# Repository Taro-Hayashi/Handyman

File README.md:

# Handyman マクロパッド ビルドガイド（[English](https://github.com/Taro-Hayashi/Handyman/blob/main/README_EN.md)）
- [キット内容](#キット内容)
- [準備](#準備)
- [はんだ付け](#はんだ付け)
- [組み立て](#組み立て)
- [キーのカスタマイズ](#キーのカスタマイズ)
- [その他](#その他)

## キット内容

||部品名|数| |
|-|-|-|-|
|1|メインボード|各1||
|2|バックプレート|1||
|3|ミドルプレート1|1||
|4|ミドルプレート2|1||
|5|保護プレート|1||
|6|ネジ（短）|9|3mm|
|7|ネジ（中）|3|5mm|
|8|ネジ（長）|12|6mm|
|9|スペーサー（短）|12|3mm|
|10|スペーサー（中）|3|4mm|
|11|ダイオード|26|1N4148|
|12|リセットスイッチ|1||
|13|ロータリーエンコーダ（ダイヤル）|1|EC11互換品|
|14|ノブ|1||
|15|ロータリーエンコーダ（ホイール）|2|EVQWGD001|
|16|ゴム足|7||
|17|Pro Micro|1||

### キット以外に必要なもの
|部品名|数||
|-|-|-|
|キースイッチ|22|[Kailh choc V1](https://shop.yushakobo.jp/collections/all-switches/products/pg1350)、[Kailh Choc V2](https://shop.yushakobo.jp/collections/all-switches/products/kailh-choc-v2)、[Lofree ロープロファイル](https://shop.yushakobo.jp/products/8381)|
|キーキャップ|22|V1は[専用キーキャップ](https://shop.yushakobo.jp/collections/keycaps/For-Choc-v1)、V2,Lofreeは[CherryMX互換](https://shop.yushakobo.jp/collections/keycaps/cherry-mx-%E4%BA%92%E6%8F%9B-%E3%82%AD%E3%83%BC%E3%82%AD%E3%83%A3%E3%83%83%E3%83%97)です。|
|Micro USB ケーブル|1||

### 必要な工具
|工具名|
|-|
|はんだごて|
|はんだ|
|精密ドライバー|
|ニッパー等ダイオードの足を切れるもの|
|マスキングテープ等絶縁できるテープ|
|エポシキ接着剤|

### オプション

LEDを光らせる場合
|部品名|数||
|-|-|-|
|[SK6812MINI-E](https://shop.yushakobo.jp/products/sk6812mini-e-10)|22|バックライト|
|[WS2812B](https://shop.yushakobo.jp/products/a0800ws-01-10)|6|アンダーグロー|

色違いのアクリルプレート
|部品名|数||
|-|-|-|
|[キーボードアクリルプレート（左手用）](https://shop.yushakobo.jp/collections/services/products/keyboard_acrylic_plate?variant=43890200740071)|||
|[キーボードアクリルプレート（右手用）](https://shop.yushakobo.jp/collections/services/products/keyboard_acrylic_plate?variant=43890207719655)|||
|[キーボードアクリルプレート（バックプレート）](https://shop.yushakobo.jp/collections/services/products/keyboard_acrylic_plate?variant=43890215583975)|||

Bluetooth接続について
 - [電池ボックスの使い方](ble.md) 

## 準備
左右どちらで作るかを選びます。  

Pro MicroはMicro-USB端子をエポシキ接着剤で補強します。  
  
両サイドと手前側のはんだ付けされてるところに少し厚めに塗ります。端子の中に入り込まないように気を付けます。
  
乾燥させている間にはんだ付けを進めましょう。  

## はんだ付け
はんだ付けのやり方は動画で見るとわかりやすいです。  
パーツは思ったより壊れないので落ち着いて作業すると失敗しにくいです。  
 - ホームセンターのDCMさんの解説動画(58秒～)  

### LEDのはんだ付け（オプション）
LEDを取り付ける場合はメインボードに最初にはんだ付けします。  
 - [LEDの取り付け方](led.md)  

### ダイオード、リセットスイッチのはんだ付け
D1からD26までダイオードを取り付けます。  
足を曲げて裏から差し込みます。  
  
ダイオードには向きがあります。三角形の先の棒と黒線を合わせましょう。  

表で更に足を曲げて抜けないようにします。  
  
ダイオードと並行に曲げるとあとでキースイッチに干渉しにくいです。

はんだ付けをして足を切ります。  

リセットスイッチを裏から差し込み表ではんだ付けします。  
  
フラックスクリーナーを使う人はここで表面を綺麗にしておきましょう。  

### ピンヘッダーのはんだ付け（Pro Microはまだはんだ付けしません）
Pro Microの取り付け場所にピンヘッダーの短い側を差し込みます。
  
位置決めのためにPro Mioroを乗せますが、はんだ付けはせず表にします。

メインボードにピンヘッダーをはんだ付けします。
  
Pro Microをいったん外します。

### キースイッチのはんだ付け

ここの二つのキースイッチは足がPro Microと干渉するので短く切ります。
  
差し込んだ状態で短く切りましょう。
  
Choc V2の場合は3本の足を、Choc V1では2本の足と固定用品の一つを短くします。

全てのスイッチをはんだ付けします。　　

### Pro Microのはんだ付け
隠れてしまうダイオードD1の方向が合っているか、キースイッチの足がはんだ付けされているかを再度確認してください。  
Micro-USB端子がショートしやすいのでカプトンテープやマスキングテープなどで絶縁します。  
  
足をニッパーで切ったらはんだ付けします。

### 動作テスト
ロータリーエンコーダーを取り付ける前にPro Microに動作ソフト（ファームウェア）を書き込んで動作確認をしましょう。  
キットとPCをUSBケーブルでつないでください。   

下のwebサイトにアクセスしてください。
- https://remap-keys.app/catalog/dTmFWd6gilf5ziDWE1TR/firmware

テストファームウェアを選んでFLASHします。

キット裏面のリセットスイッチを押すとArduino Microが現れるので、クリックして接続します（初回のみリセットスイッチを2回押す必要があることがあります）。

書き込みが完了したらウィンドウを閉じて大丈夫です。

アドレスバーやテキストエディタを使ってすべてのスイッチが反応することを確かめてください。

Remapを使ってファームウェアの更新ができない場合は、QMK Toolboxをお試しください。
- [QMK Toolboxを使ったファームウェア更新方法](firmware.md)

### ロータリーエンコーダーのはんだ付け
SW12、SW14に表からホイール型のロータリーエンコーダーを取り付けます。  
ピンの位置を確認してツメを穴に差し込みます。  

ツメを穴に引っかけてからピンを穴に差し込みます。   
   
ピンを曲げてしまわないように注意してください。  
  
差し込めたらはんだ付けします。  

SW20に表からダイヤル型のロータリーエンコーダーを取り付けて裏からはんだ付けします。  
  
クリップの部分ははんだ付けしなくても構いません。  

お疲れ様でした。再び動作を確認して問題がなければはんだ付けは終了です。

## 組み立て
USBケーブルを抜いてプレートを組付けます。  
アクリルからは保護フィルムを剥がしてください。割れやすいので気をつけましょう。  

メインボードのネジ穴にスペーサー（短）をネジ（短）で取り付けてミドルプレート1（透明）を嵌めます。
   
ここの3箇所は表側はネジではなくスペーサー（中）で止めます。

ミドルプレート2とバックプレートをネジ（長）で止めます。
 
ゴム足も貼りました。

表に保護プレートをネジ（中）で取り付けましょう。

マイナスドライバーでノブを取りつけ、キーキャップを付けたら完成です。

先ほどと同様の手順でRemap用のファームウェアに更新しましょう。
- https://remap-keys.app/catalog/dTmFWd6gilf5ziDWE1TR/firmware

## キーのカスタマイズ
こちらのサイトにGoogle Chrome（Chromiumベースのブラウザ）でアクセスしてください。
- Remap https://remap-keys.app

左を選んで進んでいくとダイアログが出てキーボードを選択できます。  
  
選択して接続してください。
  
標準ではUS配列設定でのClip Studio Paintにあわせたキーマップになっています。  

### キーマップの保存と復元
⇔アイコンで作ったキーマップを保存することができます。  
  
作ったキーマップを共有することもできるので是非お試しください。

### 左右を変える
レイアウトオプションで左右を変えることができます。  

### キーを設定する
下のキー一覧からドラッグアンドドロップし、変更が終わったら右上のflashボタンを押すと反映されます。  
  
また、USキーボードとJISキーボードはFlashの下のプルダウンから変更できます。OSの設定に合わせてください。

### 修飾キーとの組み合わせを設定する
上のキーボードのキーをクリックすると設定画面になります。
  
修飾キーと同時押ししたいキーを検索し、同時押ししたい修飾キーにチェックを入れます。

Hold-Tapもここから設定できます。

### ロータリーエンコーダーを設定する
丸いキーの左下をクリックすると時計回り、反時計回り、押し込みを切り替えることができるので、それぞれにキーを割り当てます。

### 特殊なキーを設定する
FUNCTIONSタブのVIA USER KEYにあらかじめ用意されたショートカットキーがあります。

### LEDを調整する
このボタンで発光方法を変更することができます。

## その他

### ファームウェアのフォルダ  
https://github.com/Taro-Hayashi/qmk_firmware/tree/tarohayashi/keyboards/tarohayashi/_archive/handyman

### プレートのデザインデータ  
[handyman_plates.zip](https://github.com/Taro-Hayashi/Handyman/releases/latest/download/handyman_plates.zip)  
発注先のルールに沿ってデータを修正してください。  

### 販売サイト
- 遊舎工房: https://shop.yushakobo.jp/collections/keyboard/products/2795   
- BOOTH: https://tarohayashi.booth.pm/items/3208122

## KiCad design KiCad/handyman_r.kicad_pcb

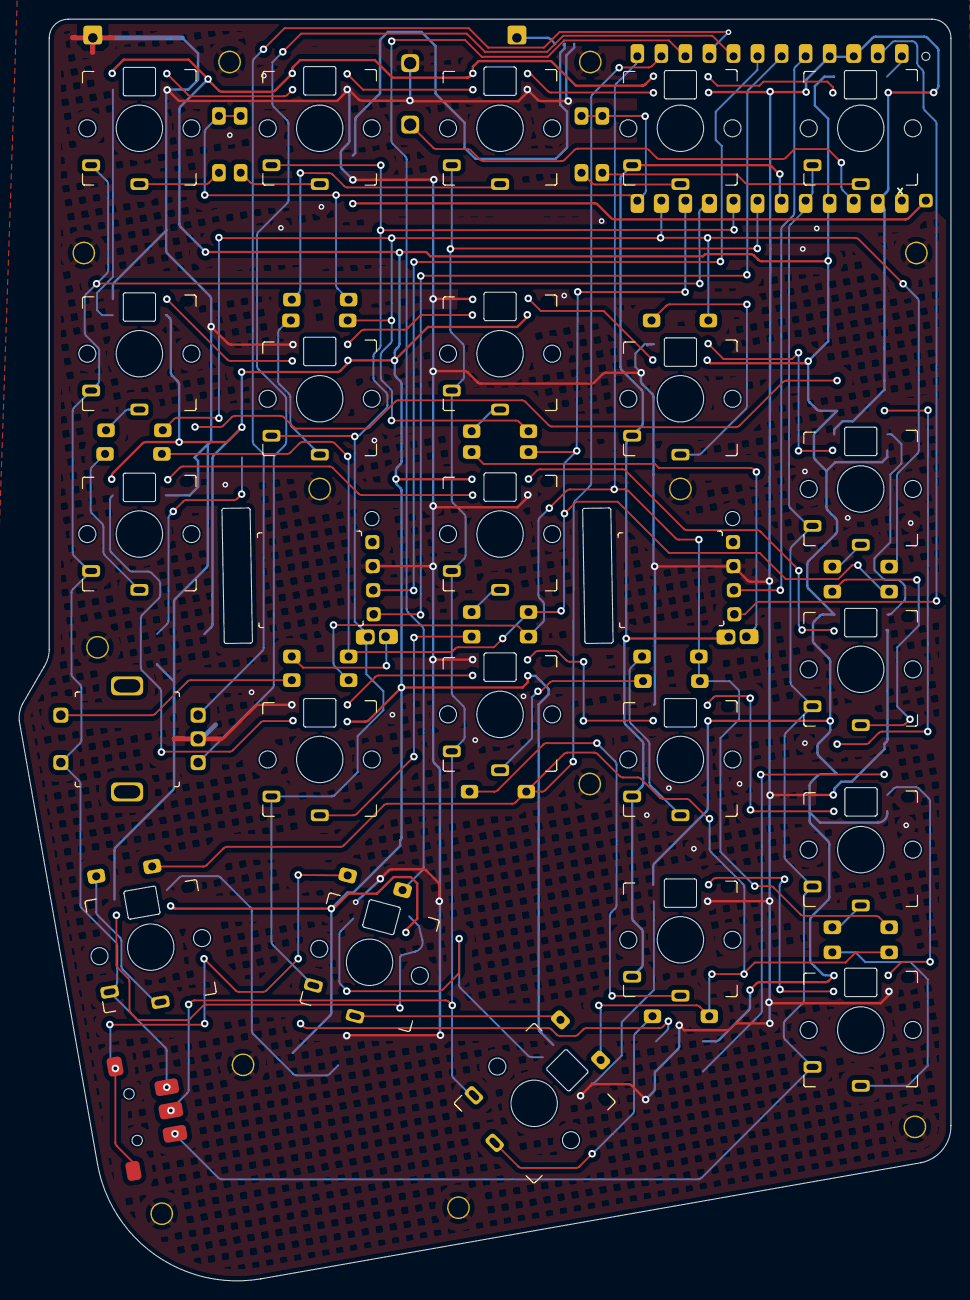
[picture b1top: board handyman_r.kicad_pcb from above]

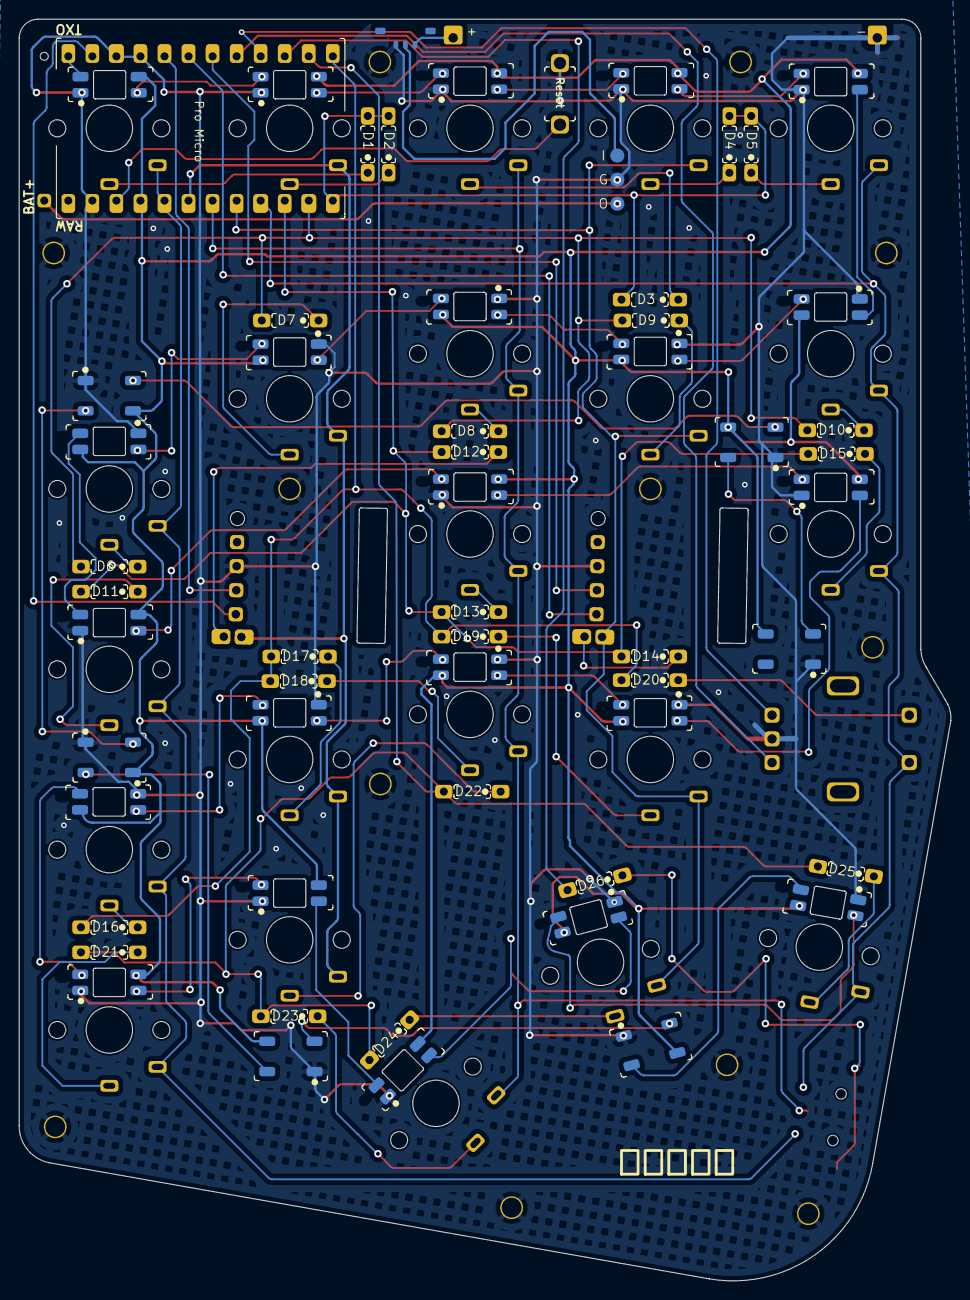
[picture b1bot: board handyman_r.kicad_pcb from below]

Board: 2 copper layers, 98.4 x 133.2 mm, 94 parts (67 on the bottom side), 74 nets.

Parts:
BL1, BL2, BL3, BL4, BL5, BL6, BL7, BL8, BL9, BL10, BL11, BL12, BL13, BL14, BL15, BL16, BL17, BL18, BL19, BL20, BL21, BL22: SK6812MINI-E; LED_SK6812MINI-E_Backlight
D1, D2, D3, D4, D5, D6, D7, D8, D9, D10, D11, D12, D13, D14, D15, D16, D17, D18, D19, D20, D21, D22, D23, D24, D25, D26: D; DIP_Diode 2
H1, H2, H3, H4, H5, H6, H7, H8, H9, H10, H11, H12: Hole; Hole_2mm_M2_PTH
Knob: Rotary_Encoder; Encoder_EC11
RST1: Reset; Switch_Reset 2
S**: SLLB120100; Switch_SLLB120100
SW1, SW2, SW3, SW4, SW5, SW6, SW7, SW8, SW9, SW10, SW11, SW13, SW15, SW16, SW17, SW18, SW19, SW21, SW22, SW23, SW24, SW25: SW_PUSH; Switch_Choc_V2only
SW12, SW14: EVQWGD001; Encoder_EVQWGD001
U1: ProMicro; MCU_BLE_Micro_Pro
UG1, UG2, UG3, UG4, UG5, UG6: WS2812B; LED_WS2812B 2

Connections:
GND: BL1.3, BL2.3, BL3.3, BL4.3, BL5.3, BL6.3, BL7.3, BL8.3, BL9.3, BL10.3, BL11.3, BL12.3, BL13.3, BL14.3, BL15.3, BL16.3, BL17.3, BL18.3, BL19.3, BL20.3, BL21.3, BL22.3, H1.1, H2.1, H3.1, H4.1, H5.1, H6.1, H7.1, H8.1, H9.1, H10.1, H11.1, H12.1, Knob.C, RST1.2, SW12.5, SW14.5, U1.3, U1.4, U1.23, UG1.3, UG2.3, UG3.3, UG4.3, UG5.3, UG6.3
unnamed: BL1.2, BL2.4
unnamed: BL2.2, BL3.4
unnamed: BL3.2, BL4.4
unnamed: BL4.2, BL5.4
unnamed: BL6.4, BL7.2
unnamed: BL7.4, BL8.2
unnamed: BL8.4, BL9.2
unnamed: BL9.4, BL10.2
unnamed: BL5.2, BL10.4
unnamed: BL11.2, BL12.4
unnamed: BL6.2, BL11.4
unnamed: BL12.2, BL13.4
unnamed: BL13.2, BL17.4
unnamed: BL14.2, BL18.4
unnamed: BL14.4, BL15.2
unnamed: BL15.4, BL16.2
unnamed: BL16.4, BL17.2
unnamed: BL18.2, BL19.4
unnamed: BL19.2, BL20.4
unnamed: BL20.2, BL21.4
unnamed: BL21.2, BL22.4
unnamed: BL22.2, UG6.4
unnamed: D1.1, SW1.2
unnamed: D2.1, SW2.2
unnamed: D3.1, SW3.2
unnamed: D4.1, SW4.2
unnamed: D5.1, SW5.2
unnamed: D6.1, SW6.2
unnamed: D7.1, SW7.2
unnamed: D8.1, SW8.2
unnamed: D9.1, SW9.2
unnamed: D10.1, SW10.2
unnamed: D11.1, SW11.2
unnamed: D12.1, SW12.1
unnamed: D13.1, SW13.2
unnamed: D14.1, SW14.1
unnamed: D15.1, SW15.2
unnamed: D16.1, SW16.2
unnamed: D17.1, SW17.2
unnamed: D18.1, SW18.2
unnamed: D19.1, SW19.2
unnamed: D20.1, Knob.S1
unnamed: D21.1, SW21.2
unnamed: D22.1, SW22.2
unnamed: D23.1, SW23.2
unnamed: D24.1, SW24.2
unnamed: D25.1, SW25.2
unnamed: UG1.4, UG2.2
unnamed: UG2.4, UG3.2
unnamed: UG3.4, UG4.2
unnamed: UG4.4, UG5.2
unnamed: UG5.4, UG6.2
VCC: BL1.1, BL2.1, BL3.1, BL4.1, BL5.1, BL6.1, BL7.1, BL8.1, BL9.1, BL10.1, BL11.1, BL12.1, BL13.1, BL14.1, BL15.1, BL16.1, BL17.1, BL18.1, BL19.1, BL20.1, BL21.1, BL22.1, U1.21, UG1.1, UG2.1, UG3.1, UG4.1, UG5.1, UG6.1
col0: S**.1, SW1.1, SW6.1, SW11.1, SW16.1, SW21.1, U1.20
col1: SW2.1, SW7.1, SW12.2, SW17.1, SW22.1, U1.19
col2: S**.3, SW3.1, SW8.1, SW13.1, SW18.1, SW23.1, U1.18
col3: SW4.1, SW9.1, SW14.2, SW19.1, SW24.1, U1.17
col4: Knob.S2, S**.2, SW5.1, SW10.1, SW15.1, SW25.1, U1.16
lbc1: D26.1, S**.4
led: BL1.4, U1.1
reset: RST1.1, U1.22
ro1a: SW12.3, U1.2
ro1b: SW12.4, U1.5
ro2a: SW14.3, U1.6
ro2b: SW14.4, U1.7
ro3a: Knob.A, U1.8
ro3b: Knob.B, U1.9
row0: D1.2, D2.2, D3.2, D4.2, D5.2, U1.13
row1: D6.2, D7.2, D8.2, D9.2, D10.2, U1.14
row2: D11.2, D12.2, D13.2, D14.2, D15.2, U1.15
row3: D16.2, D17.2, D18.2, D19.2, D20.2, U1.12
row4: D21.2, D22.2, D23.2, D24.2, D25.2, U1.11
row5: D26.2, U1.10

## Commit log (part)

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2021-09-13 URL更新
2021-10-25 remap
2021-11-23 img_r
2021-12-23 del img
2021-12-30 Errors in the build procedure
2022-12-10 Create README_DRAFT
2022-12-10 Update README_DRAFT
2023-09-25 0.22.5
2026-05-24 Add hardware and firmware files
